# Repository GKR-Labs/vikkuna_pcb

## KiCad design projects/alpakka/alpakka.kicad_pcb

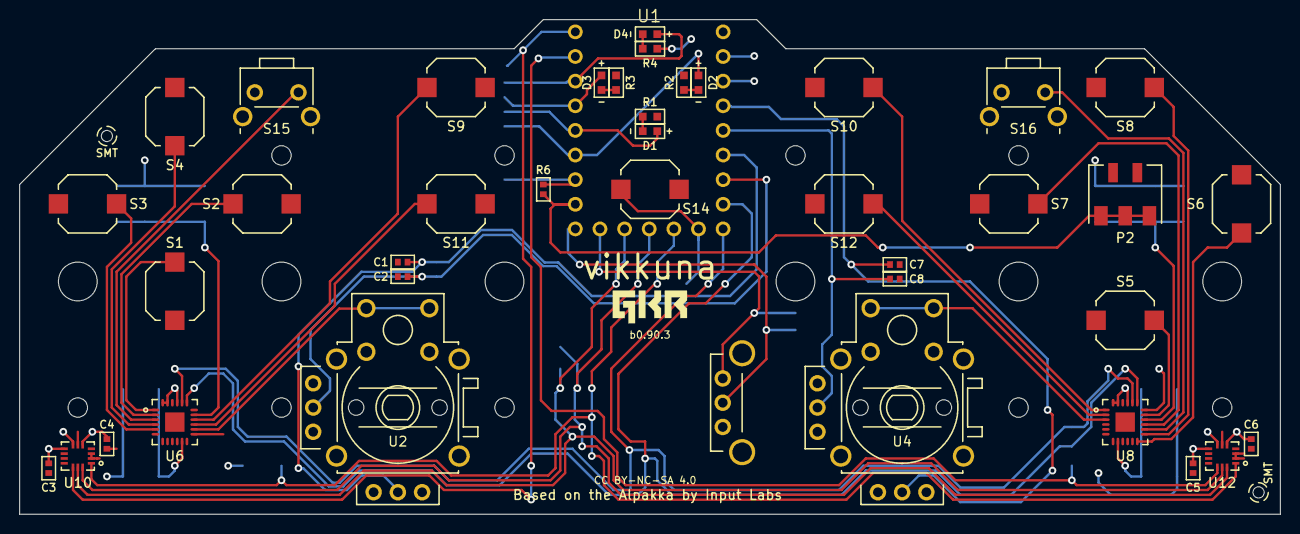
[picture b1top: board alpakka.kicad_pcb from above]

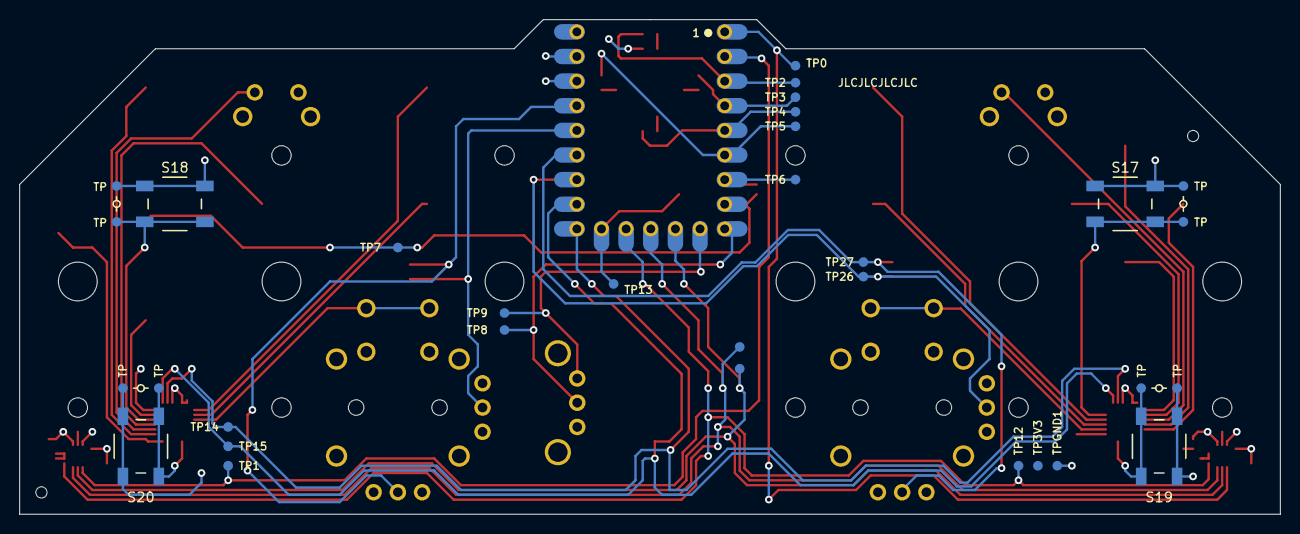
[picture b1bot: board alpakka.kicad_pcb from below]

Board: 2 copper layers, 130.0 x 51.0 mm, 73 parts (33 on the bottom side), 46 nets.

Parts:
C1, C2, C3, C4, C5, C6, C7, C8: C; 0402
D1, D2, D3, D4: Diode; 0603_d
P2: Endpoint; HRO_BC-25-3P
R1, R2, R3, R4: R; 0603
R6: R6; 0402
S1: down; Alpsalpine_SKPM
S2: right; Alpsalpine_SKPM
S3: left; Alpsalpine_SKPM
S4: up; Alpsalpine_SKPM
S5: a; Alpsalpine_SKPM
S6: b; Alpsalpine_SKPM
S7: x; Alpsalpine_SKPM
S8: y; Alpsalpine_SKPM
S9: select_1; Alpsalpine_SKPM
S10: start_1; Alpsalpine_SKPM
S11: select_2; Alpsalpine_SKPM
S12: start_2; Alpsalpine_SKPM
S14: home; Alpsalpine_SKPM
S15: l1; Alpsalpine_SKHHL
S16: r1; Alpsalpine_SKHHL
S17: l2; Alpsalpine_SKQG
S18: r2; Alpsalpine_SKQG
S19: l4; Alpsalpine_SKQG
S20: r4; Alpsalpine_SKQG
TP0, TP1, TP2, TP3, TP3V3, TP4, TP5, TP6, TP7, TP8, TP9, TP10, TP11, TP12, TP13, TP14, TP15, TP26, TP27, TP101, TP102, TP103, TP104, TP201, TP202, TP203, TP204: Endpoint; Pad_1mm
TPGND1: Endpoint; Pad_1mm
U1: 微雪RP2040-ZERO; PICOMINI
U2, U4: Alpsalpine_RKJXV; Alpsalpine_RKJXV122400R
U3: Alpsalpine_EC10E
U6, U8: NXP_PCAL6416A; QFN24
U10, U12: ST_LSM6; LGA14

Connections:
A0: S1.2, U6.1 (P0)
A1: S2.2, U6.2 (P1)
A2: S15.2, U6.3 (P2)
A3: S4.2, U6.4 (P3)
A4: S3.2, U6.5 (P4)
A9: S19.2, TP204.1, U6.11 (P9)
A12: U2.8 (B), U2.10 (D), U6.14 (P12)
A13: S11.2, U6.15 (P13)
A14: S9.2, U6.16 (P14)
A15: S17.2, TP202.1, U6.17 (P15)
ADC0: C2.2, TP26.1, U1.16 (GP26), U2.2 (ADC0)
ADC1: C1.2, TP27.1, U1.17 (GP27), U2.5 (ADC1)
ADC2: C8.2, U1.18 (GP28), U4.2 (ADC0)
ADC3: C7.2, U1.19 (GP29), U4.5 (ADC1)
B0: S10.2, U8.1 (P0)
B1: S12.2, U8.2 (P1)
B2: U4.8 (B), U4.10 (D), U8.3 (P2)
B7: S20.2, TP104.1, U8.8 (P7)
B10: S6.2, U8.12 (P10)
B11: S8.2, U8.13 (P11)
B12: S16.2, U8.14 (P12)
B13: S7.2, U8.15 (P13)
B14: S18.2, TP102.1, U8.16 (P14)
B15: S5.2, U8.17 (P15)
CS0: TP0.1, U1.0 (GP0), U10.12 (CS)
CS1: TP1.1, U1.1 (GP1), U12.12 (CS)
GND: C1.1, C2.1, C3.1, C4.1, C5.1, C6.1, C7.1, C8.1, R1.1, R2.1, R3.1, R4.1, S1.1, S2.1, S3.1, S4.1, S5.1, S6.1, S7.1, S8.1, S9.1, S10.1, S11.1, S12.1, S14.1, S15.1, S16.1, S17.1, S18.1, S19.1, S20.1, TP101.1, TP103.1, TP201.1, TP203.1, TPGND1.1, U1.21 (GND), U2.1 (GND0), U2.4 (GND1), U2.7 (A), U2.9 (C), U3.3 (GND), U4.1 (GND0), U4.4 (GND1), U4.7 (A), U4.9 (C), U6.9 (VSS), U6.13 (P11), U6.18 (ADDR), U8.9 (VSS), U10.2 (SDx), U10.3 (SCx), U10.6 (GNDIO), U10.7 (GND), U12.2 (SDx), U12.3 (SCx), U12.6 (GNDIO), U12.7 (GND)
GP2: D4.2 (A), TP2.1, U1.2 (GP2)
GP3: D3.2 (A), TP3.1, U1.3 (GP3)
GP4: D1.2 (A), TP4.1, U1.4 (GP4)
GP5: D2.2 (A), TP5.1, U1.5 (GP5)
GP6: R6.1, TP6.1, U1.6 (GP6)
GP7: P2.1, R6.2, TP7.1, U1.7 (GP7)
GP8: TP8.1, U1.8 (GP8), U3.2 (B)
GP9: TP9.1, U1.9 (GP9), U3.1 (A)
GP20: S14.2, TP13.1, U1.13 (GP13)
I2C_SCL: TP15.1, U1.15 (GP15), U6.19 (SCL), U8.19 (SCL)
I2C_SDA: TP14.1, U1.14 (GP14), U6.20 (SDA), U8.20 (SDA)
unnamed: D1.1 (K), R1.2
unnamed: D2.1 (K), R2.2
unnamed: D3.1 (K), R3.2
unnamed: D4.1 (K), R4.2
SPI_CK: TP10.1, U1.10 (GP10), U10.13 (SCL), U12.13 (SCL)
SPI_RX: TP12.1, U1.12 (GP12), U10.1 (SDO), U12.1 (SDO)
SPI_TX: TP11.1, U1.11 (GP11), U10.14 (SDA), U12.14 (SDA)
VCC: C3.2, C4.2, C5.2, C6.2, TP3V3.1, U1.20 (3V3), U2.3 (VCC0), U2.6 (VCC1), U4.3 (VCC0), U4.6 (VCC1), U6.21 (VDD), U6.23 (VDDBUS), U6.24 (RESET), U8.18 (ADDR), U8.21 (VDD), U8.23 (VDDBUS), U8.24 (RESET), U10.5 (VDDIO), U10.8 (VDD), U12.5 (VDDIO), U12.8 (VDD)

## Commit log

2024-09-08 Longmao's dual_thumbstick_mod_for_rp2040_picomini
2025-04-02 Cleanup and silkscreen tweaks
2025-07-24 Port to KiCad 9

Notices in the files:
projects/alpakka/alpakka.kicad_pcb:
CC BY-NC-SA 4.0
